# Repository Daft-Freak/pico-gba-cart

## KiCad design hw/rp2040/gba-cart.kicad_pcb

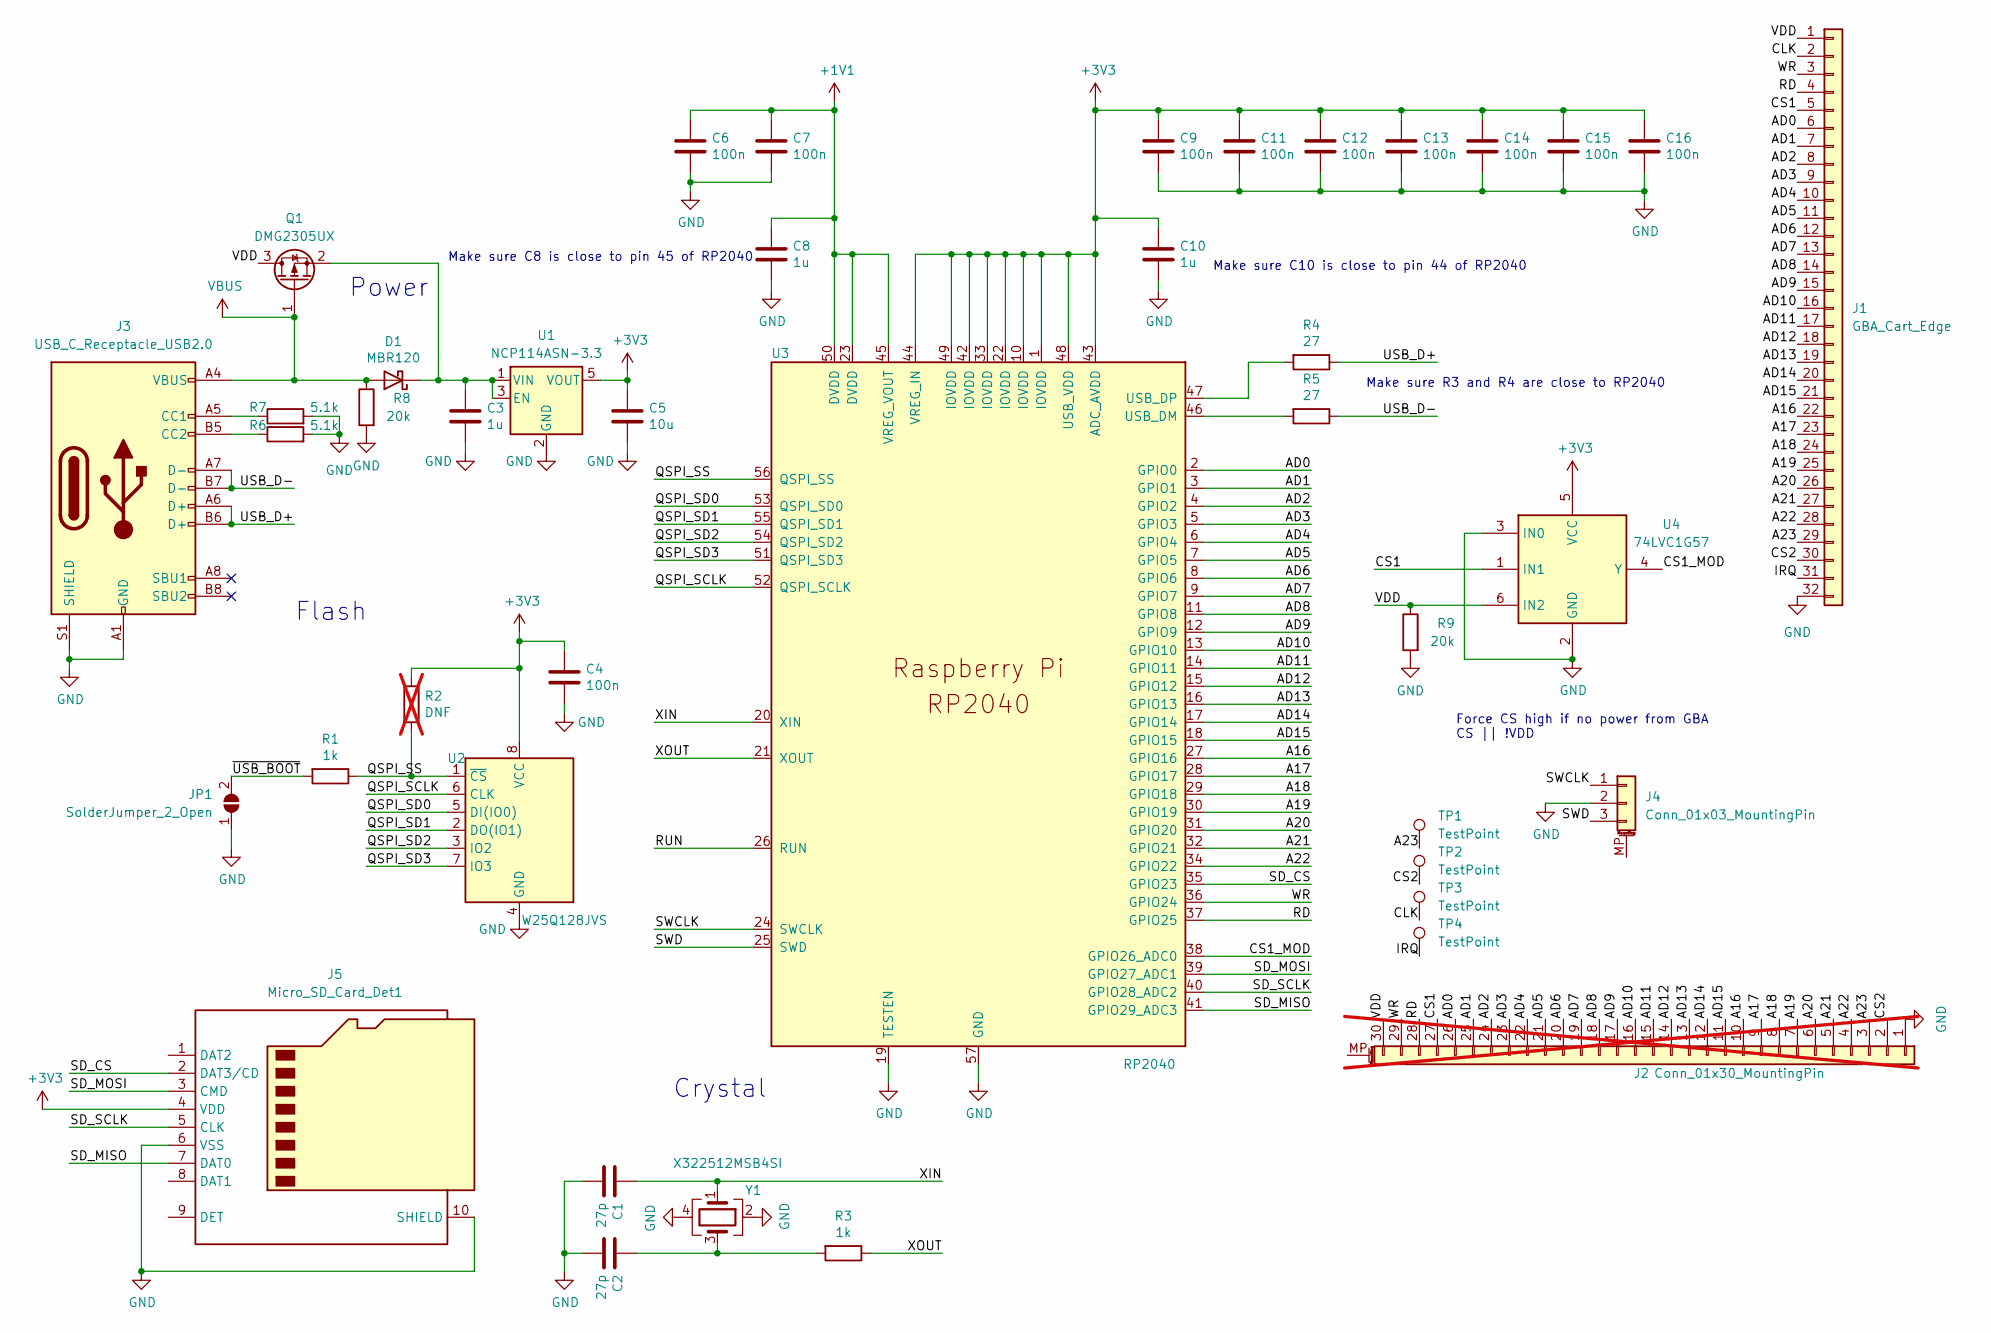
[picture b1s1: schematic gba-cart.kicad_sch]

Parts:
C1, C2: 27p; C_0402_1005Metric
C3: 1u; C_0805_2012Metric
C4, C6, C7, C9, C11, C12, C13, C14, C15, C16: 100n; C_0402_1005Metric
C5: 10u; C_0805_2012Metric
C8, C10: 1u; C_0402_1005Metric
D1: MBR120; MBR120_SOD-123
J1: GBA_Cart_Edge
J2: Conn_01x30_MountingPin; JUSHUO_AFC01-S30FCA-00_1x30-1MP_P0.50mm_Horizontal; not fitted
J3: USB_C_Receptacle_USB2.0; USB_C_Receptacle_HRO_TYPE-C-31-M-12
J4: Conn_01x03_MountingPin; JST_SH_SM03B-SRSS-TB_1x03-1MP_P1.00mm_Horizontal
J5: Micro_SD_Card_Det1; microSD_HC_Push
JP1: SolderJumper_2_Open; SolderJumper-2_P1.3mm_Open_Pad1.0x1.5mm
Q1: DMG2305UX; SOT-23
R1, R3: 1k; C_0402_1005Metric
R2: DNF; C_0402_1005Metric; not fitted
R4, R5: 27; C_0402_1005Metric
R6, R7: 5.1k; R_0402_1005Metric
R8, R9: 20k; R_0402_1005Metric
TP1, TP2, TP3, TP4: TestPoint; TestPoint_Pad_1.0x1.0mm
U1: NCP114ASN-3.3; TSOP-5_1.65x3.05mm_P0.95mm
U2: W25Q128JVS; SOIC-8_5.23x5.23mm_P1.27mm
U3: RP2040; RP2040-QFN-56
U4: 74LVC1G57; SOT-23-6
Y1: X322512MSB4SI; Crystal_SMD_3225-4Pin_3.2x2.5mm

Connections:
+1V1: C6.1, C7.1, C8.1, U3.23 (DVDD), U3.45 (VREG_VOUT), U3.50 (DVDD)
+3V3: C4.1, C5.1, C9.1, C10.1, C11.1, C12.1, C13.1, C14.1, C15.1, C16.1, J5.4 (VDD), R2.1, U1.5 (VOUT), U2.8 (VCC), U3.1 (IOVDD), U3.10 (IOVDD), U3.22 (IOVDD), U3.33 (IOVDD), U3.42 (IOVDD), U3.43 (ADC_AVDD), U3.44 (VREG_IN), U3.48 (USB_VDD), U3.49 (IOVDD), U4.5 (VCC)
/A16: J1.22, J2.10, U3.27 (GPIO16)
/A17: J1.23, J2.9, U3.28 (GPIO17)
/A18: J1.24, J2.8, U3.29 (GPIO18)
/A19: J1.25, J2.7, U3.30 (GPIO19)
/A20: J1.26, J2.6, U3.31 (GPIO20)
/A21: J1.27, J2.5, U3.32 (GPIO21)
/A22: J1.28, J2.4, U3.34 (GPIO22)
/A23: J1.29, J2.3, TP1.1
/AD0: J1.6, J2.26, U3.2 (GPIO0)
/AD1: J1.7, J2.25, U3.3 (GPIO1)
/AD2: J1.8, J2.24, U3.4 (GPIO2)
/AD3: J1.9, J2.23, U3.5 (GPIO3)
/AD4: J1.10, J2.22, U3.6 (GPIO4)
/AD5: J1.11, J2.21, U3.7 (GPIO5)
/AD6: J1.12, J2.20, U3.8 (GPIO6)
/AD7: J1.13, J2.19, U3.9 (GPIO7)
/AD8: J1.14, J2.18, U3.11 (GPIO8)
/AD9: J1.15, J2.17, U3.12 (GPIO9)
/AD10: J1.16, J2.16, U3.13 (GPIO10)
/AD11: J1.17, J2.15, U3.14 (GPIO11)
/AD12: J1.18, J2.14, U3.15 (GPIO12)
/AD13: J1.19, J2.13, U3.16 (GPIO13)
/AD14: J1.20, J2.12, U3.17 (GPIO14)
/AD15: J1.21, J2.11, U3.18 (GPIO15)
/CLK: J1.2, TP3.1
/CS1: J1.5, J2.27, U4.1 (IN1)
/CS1_MOD: U3.38 (GPIO26_ADC0), U4.4 (Y)
/CS2: J1.30, J2.2, TP2.1
/IRQ: J1.31, TP4.1
/QSPI_SCLK: U2.6 (CLK), U3.52 (QSPI_SCLK)
/QSPI_SD0: U2.5 (DI(IO0)), U3.53 (QSPI_SD0)
/QSPI_SD1: U2.2 (DO(IO1)), U3.55 (QSPI_SD1)
/QSPI_SD2: U2.3 (IO2), U3.54 (QSPI_SD2)
/QSPI_SD3: U2.7 (IO3), U3.51 (QSPI_SD3)
/QSPI_SS: R1.1, R2.2, U2.1 (~CS), U3.56 (QSPI_SS)
/RD: J1.4, J2.28, U3.37 (GPIO25)
/RUN: U3.26 (RUN)
/SD_CS: J5.2 (DAT3/CD), U3.35 (GPIO23)
/SD_MISO: J5.7 (DAT0), U3.41 (GPIO29_ADC3)
/SD_MOSI: J5.3 (CMD), U3.39 (GPIO27_ADC1)
/SD_SCLK: J5.5 (CLK), U3.40 (GPIO28_ADC2)
/SWCLK: J4.1, U3.24 (SWCLK)
/SWD: J4.3, U3.25 (SWD)
/USB_D+: J3.A6 (D+), J3.B6 (D+), R4.1
/USB_D-: J3.A7 (D-), J3.B7 (D-), R5.1
/VDD: J1.1, J2.30, Q1.3 (D), R9.1, U4.6 (IN2)
/WR: J1.3, J2.29, U3.36 (GPIO24)
/XIN: C1.1, U3.20 (XIN), Y1.1
/XOUT: R3.1, U3.21 (XOUT)
/~USB_BOOT: JP1.2 (B), R1.2
GND: C1.2, C2.2, C3.2, C4.2, C5.2, C6.2, C7.2, C8.2, C9.2, C10.2, C11.2, C12.2, C13.2, C14.2, C15.2, C16.2, J1.32, J3.A1 (GND), J3.A12 (GND), J3.B1 (GND), J3.B12 (GND), J3.S1 (SHIELD), J4.2, J5.6 (VSS), J5.10 (SHIELD), JP1.1 (A), R6.2, R7.2, R8.2, R9.2, U1.2 (GND), U2.4 (GND), U3.19 (TESTEN), U3.57 (GND), U4.2 (GND), U4.3 (IN0), Y1.2, Y1.4
unnamed: C2.1, R3.2, Y1.3
unnamed: C3.1, D1.1 (K), Q1.2 (S), U1.1 (VIN), U1.3 (EN)
unnamed: J3.A5 (CC1), R7.1
unnamed: J3.B5 (CC2), R6.1
unnamed: R5.2, U3.46 (USB_DM)
unnamed: R4.2, U3.47 (USB_DP)
VBUS: D1.2 (A), J3.A4 (VBUS), J3.A9 (VBUS), J3.B4 (VBUS), J3.B9 (VBUS), Q1.1 (G), R8.1

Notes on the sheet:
Crystal
Flash
Power
Make sure R3 and R4 are close to RP2040
Force CS high if no power from GBA CS || !VDD
Make sure C10 is close to pin 44 of RP2040
Make sure C8 is close to pin 45 of RP2040

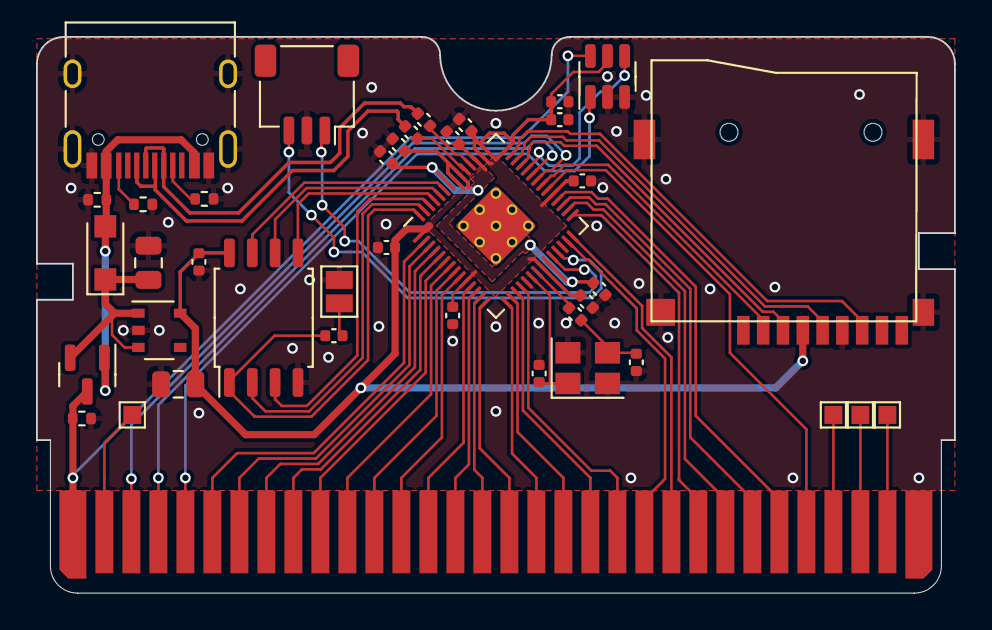
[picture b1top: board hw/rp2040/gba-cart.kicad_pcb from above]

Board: 2 copper layers, 51.0 x 30.9 mm, 40 parts (0 on the bottom side), 59 nets.

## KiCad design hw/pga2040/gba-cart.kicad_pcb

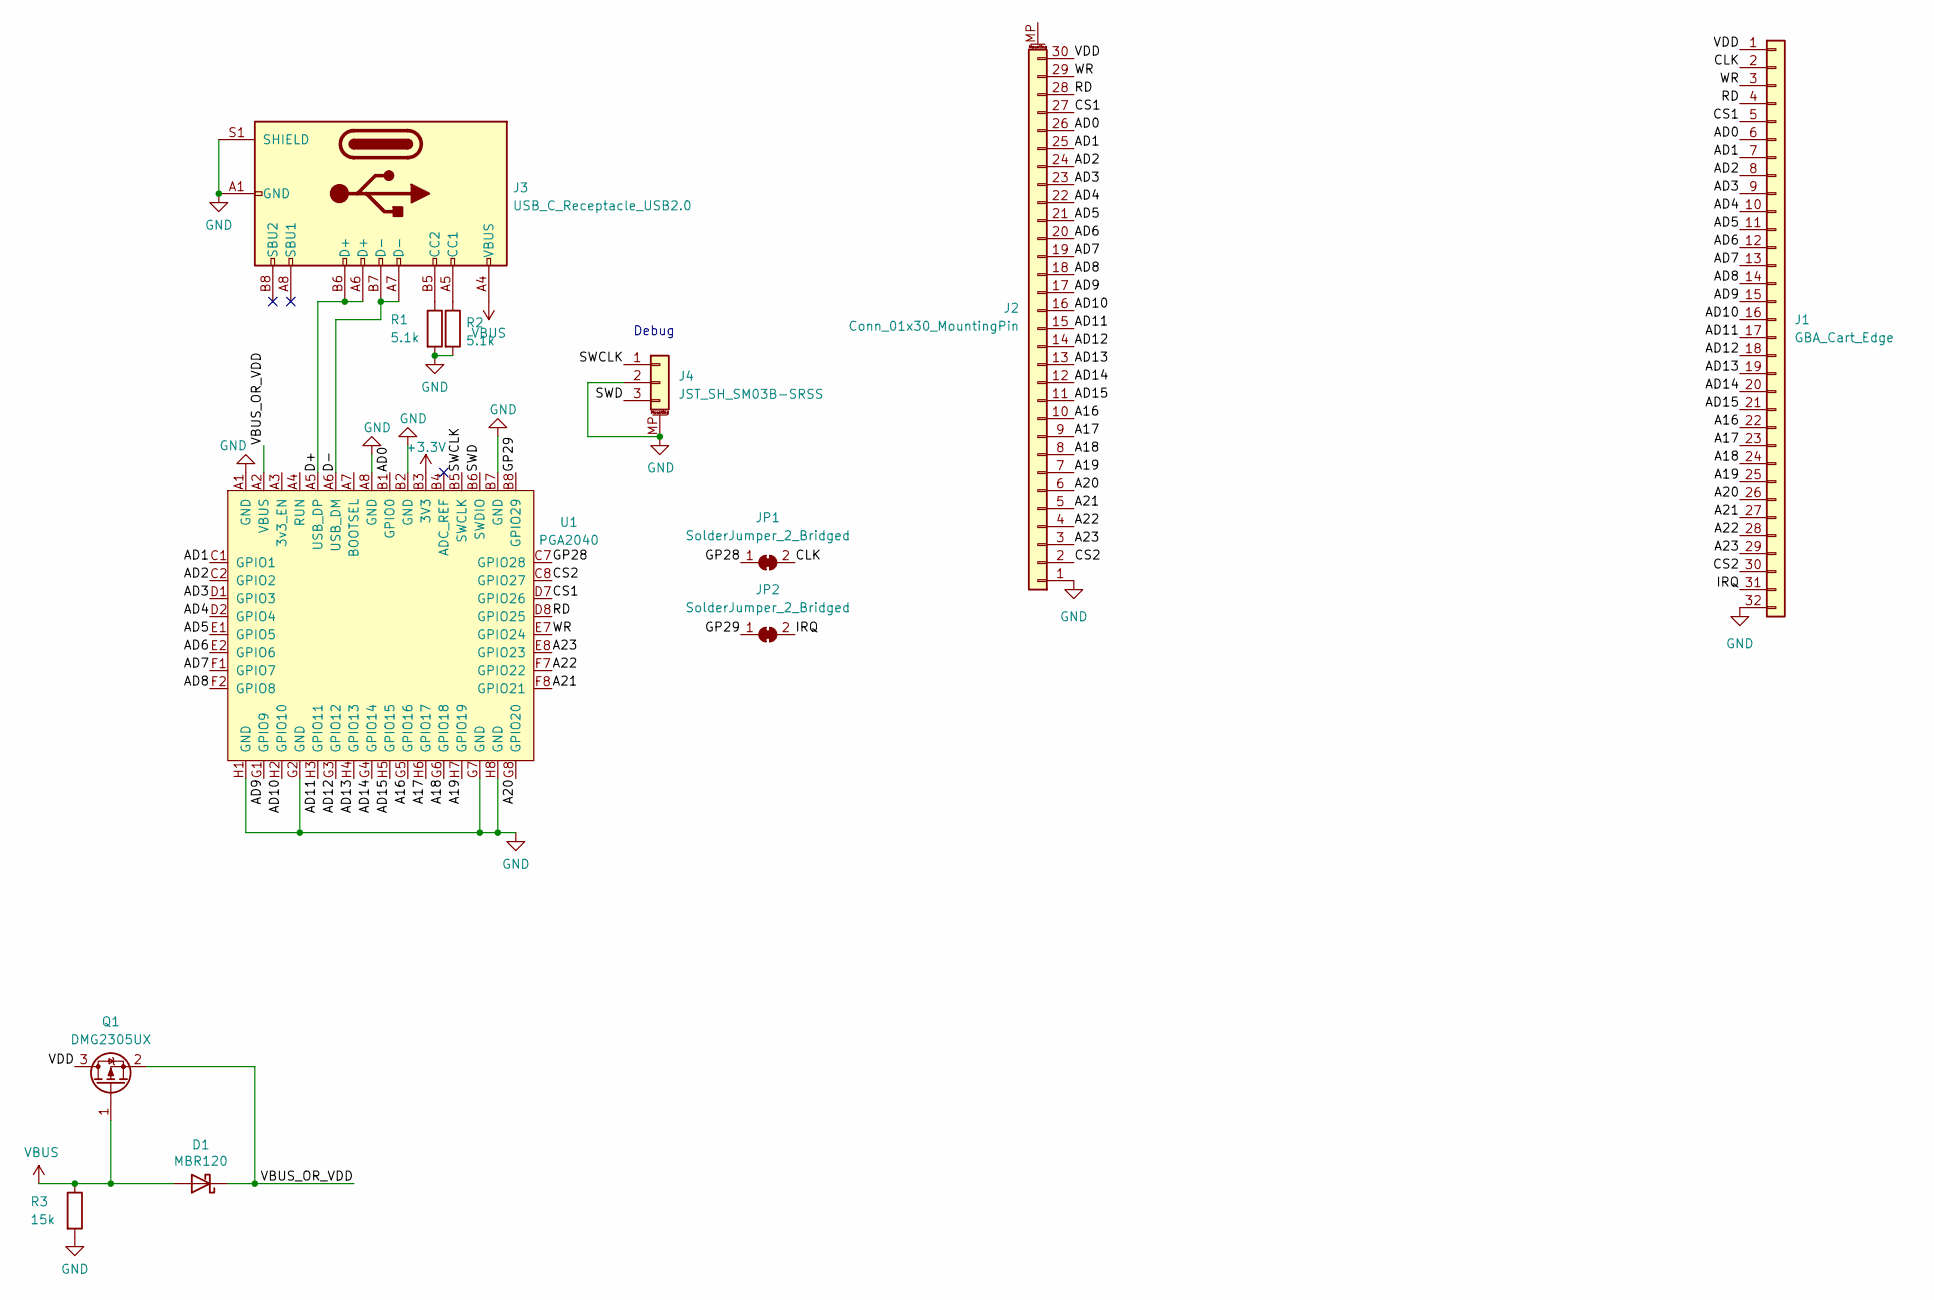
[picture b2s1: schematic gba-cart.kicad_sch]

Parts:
D1: MBR120; MBR120_SOD-123
J1: GBA_Cart_Edge
J2: Conn_01x30_MountingPin; JUSHUO_AFC01-S30FCA-00_1x30-1MP_P0.50mm_Horizontal
J3: USB_C_Receptacle_USB2.0; USB_C_Receptacle_HRO_TYPE-C-31-M-12
J4: JST_SH_SM03B-SRSS; JST_SH_SM03B-SRSS-TB_1x03-1MP_P1.00mm_Horizontal
JP1, JP2: SolderJumper_2_Bridged; SolderJumper-2_P1.3mm_Bridged_Pad1.0x1.5mm
Q1: DMG2305UX; SOT-23
R1, R2: 5.1k; R_0402_1005Metric
R3: 15k; R_0402_1005Metric
U1: PGA2040; PGA2040_PTH_WITH_SLOT

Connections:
+3V3: U1.B3 (3V3)
/A16: J1.22, J2.10, U1.G5 (GPIO16)
/A17: J1.23, J2.9, U1.H6 (GPIO17)
/A18: J1.24, J2.8, U1.G6 (GPIO18)
/A19: J1.25, J2.7, U1.H7 (GPIO19)
/A20: J1.26, J2.6, U1.G8 (GPIO20)
/A21: J1.27, J2.5, U1.F8 (GPIO21)
/A22: J1.28, J2.4, U1.F7 (GPIO22)
/A23: J1.29, J2.3, U1.E8 (GPIO23)
/AD0: J1.6, J2.26, U1.B1 (GPIO0)
/AD1: J1.7, J2.25, U1.C1 (GPIO1)
/AD2: J1.8, J2.24, U1.C2 (GPIO2)
/AD3: J1.9, J2.23, U1.D1 (GPIO3)
/AD4: J1.10, J2.22, U1.D2 (GPIO4)
/AD5: J1.11, J2.21, U1.E1 (GPIO5)
/AD6: J1.12, J2.20, U1.E2 (GPIO6)
/AD7: J1.13, J2.19, U1.F1 (GPIO7)
/AD8: J1.14, J2.18, U1.F2 (GPIO8)
/AD9: J1.15, J2.17, U1.G1 (GPIO9)
/AD10: J1.16, J2.16, U1.H2 (GPIO10)
/AD11: J1.17, J2.15, U1.H3 (GPIO11)
/AD12: J1.18, J2.14, U1.G3 (GPIO12)
/AD13: J1.19, J2.13, U1.H4 (GPIO13)
/AD14: J1.20, J2.12, U1.G4 (GPIO14)
/AD15: J1.21, J2.11, U1.H5 (GPIO15)
/CLK: J1.2, JP1.2 (B)
/CS1: J1.5, J2.27, U1.D7 (GPIO26)
/CS2: J1.30, J2.2, U1.C8 (GPIO27)
/D+: J3.A6 (D+), J3.B6 (D+), U1.A5 (USB_DP)
/D-: J3.A7 (D-), J3.B7 (D-), U1.A6 (USB_DM)
/GP28: JP1.1 (A), U1.C7 (GPIO28)
/GP29: JP2.1 (A), U1.B8 (GPIO29)
/IRQ: J1.31, JP2.2 (B)
/RD: J1.4, J2.28, U1.D8 (GPIO25)
/SWCLK: J4.1, U1.B5 (SWCLK)
/SWD: J4.3, U1.B6 (SWDIO)
/VBUS_OR_VDD: D1.1 (K), Q1.2 (S), U1.A2 (VBUS)
/VDD: J1.1, J2.30, Q1.3 (D)
/WR: J1.3, J2.29, U1.E7 (GPIO24)
GND: J1.32, J2.1, J3.A1 (GND), J3.A12 (GND), J3.B1 (GND), J3.B12 (GND), J3.S1 (SHIELD), J4.2, J4.MP (MountPin), R1.2, R2.2, R3.2, U1.A1 (GND), U1.A8 (GND), U1.B2 (GND), U1.B7 (GND), U1.G2 (GND), U1.G7 (GND), U1.H1 (GND), U1.H8 (GND)
unnamed: J3.A5 (CC1), R2.1
unnamed: J3.B5 (CC2), R1.1
VBUS: D1.2 (A), J3.A4 (VBUS), J3.A9 (VBUS), J3.B4 (VBUS), J3.B9 (VBUS), Q1.1 (G), R3.1

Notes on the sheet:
Debug

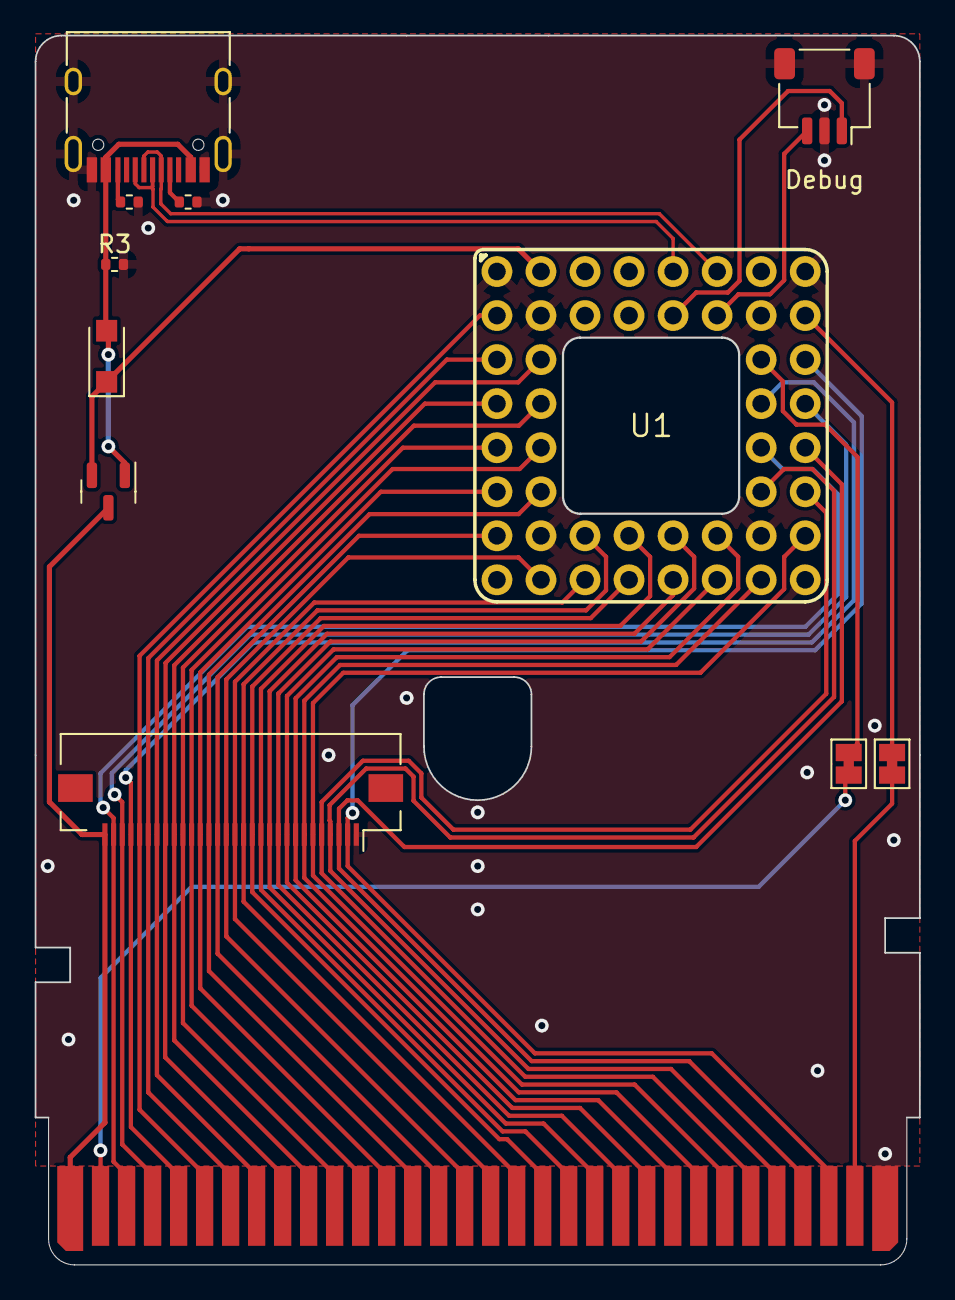
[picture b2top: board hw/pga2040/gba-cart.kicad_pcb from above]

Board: 2 copper layers, 51.0 x 70.9 mm, 12 parts (0 on the bottom side), 42 nets.

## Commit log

2025-03-29 Add PGA2040 prototype
2025-03-29 Add RP2040-based board
2025-04-02 Add missing include for set_sys_closk_khz
2025-04-02 Workaround CMake 4.0 when building ROM
    Really should update to gba-toolchain v4
2025-04-02 Deduplicate pin definitions
2025-04-03 Use custom linker script to put the GBA ROM at the start of RAM
    Also adds a PSRAM region
2025-04-03 Use the PIO to shift in the high bits of the address, remove sniffer usage
    Decreases read setup time enough to run with 3 wait states for non-sequential access
2025-04-04 Save a cycle and 2 instrs in rd program
    By using the new MOV PINDIRS
2025-06-17 Download GBA toolchain if not specified
    Doesn't quite work due to old version/new cmake problems
2025-06-17 Update gba-toolchain
2025-06-17 Add a build action
    Let's see if this works...
2025-06-17 Fix rom build
    Need to install to get the .gba file.
2025-06-17 Hopefully fix build with make
    Always use ninja so hadn't noticed this
2025-06-17 Install something
    Mostly so the action doesn't fail. Everything is broken because of a bug in libseven though.
